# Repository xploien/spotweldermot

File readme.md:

# Spotwelder 
design progress of a MOT based spot welder 

## Feautres / Roadmap 

- [] precise digital control
- [] casing / enclosure 
- [] manual mode 
- [] cheap / easy to make as posible 

## Notes 

teoretical circuit is up, some simulation regarding the zero cross voltage detector have been done in circuit simulato Qucs-s
, power control baord needs X class capacitors to be safer, case is going to be hard since Mot transformer is really heavy. 

### some design concepts (Not final Product)

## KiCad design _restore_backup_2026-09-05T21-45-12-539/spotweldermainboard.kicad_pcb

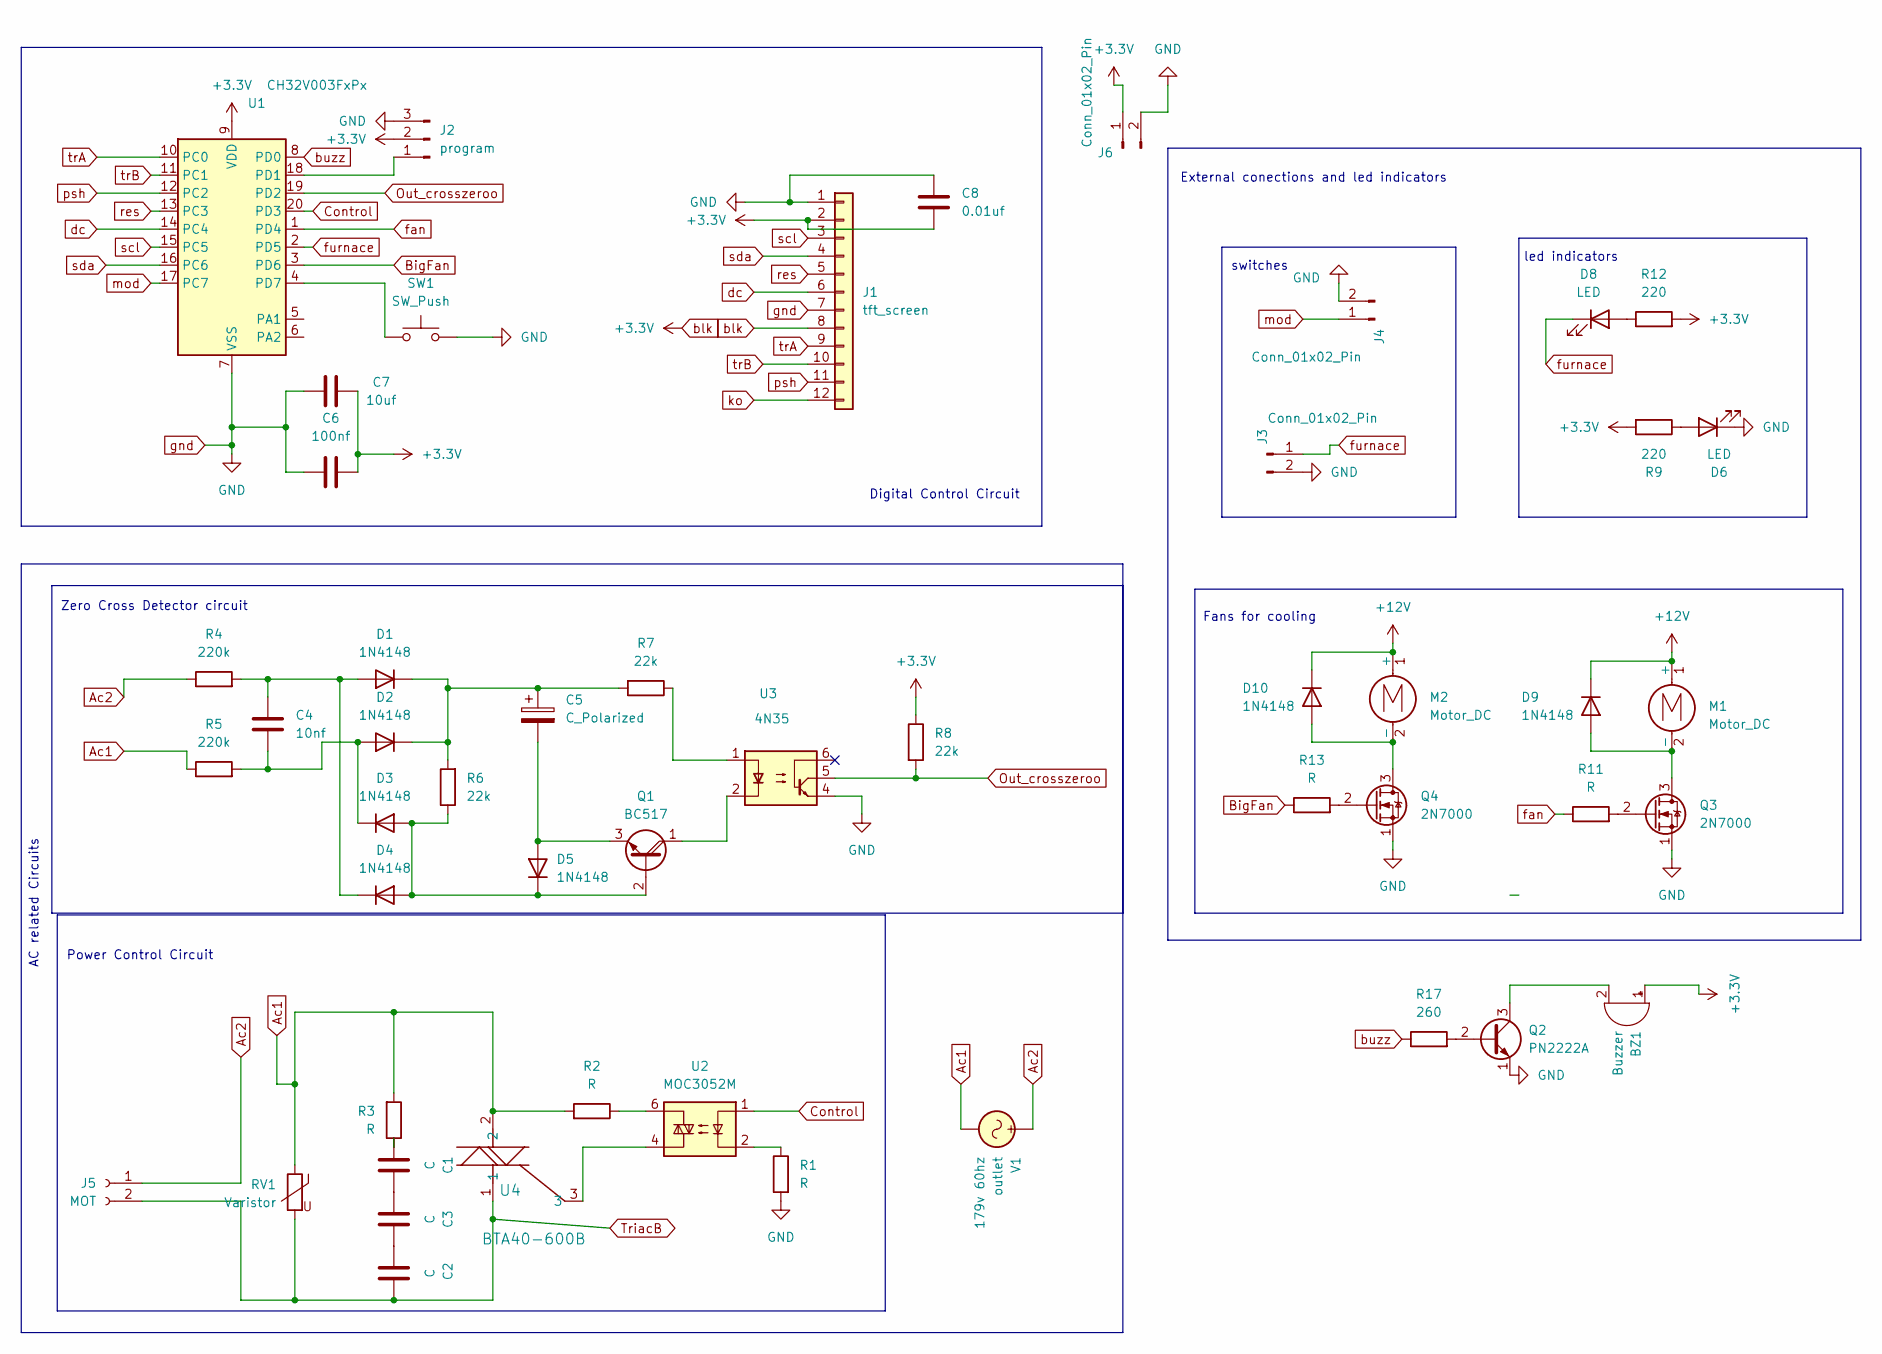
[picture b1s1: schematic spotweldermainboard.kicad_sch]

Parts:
BZ1: Buzzer; Buzzer_12x9.5RM7.6
C1, C2, C3: C; C_Rect_L18.0mm_W9.0mm_P15.00mm_FKS3_FKP3
C4: 10nf; C_Disc_D5.0mm_W2.5mm_P5.00mm
C5: C_Polarized; CP_Radial_D4.0mm_P2.00mm
C6: 100nf; CP_Radial_D4.0mm_P2.00mm
C7: 10uf; CP_Radial_D4.0mm_P2.00mm
C8: 0.01uf; C_Disc_D5.0mm_W2.5mm_P5.00mm
D1, D2, D3, D4, D5, D9, D10: 1N4148; D_DO-35_SOD27_P7.62mm_Horizontal
D6, D8: LED; LED_0402_1005Metric_Pad0.77x0.64mm_HandSolder
J1: tft_screen; PinSocket_1x12_P2.54mm_Horizontal
J2: program; PinHeader_1x03_P2.54mm_Vertical
J3, J4, J6: Conn_01x02_Pin; TerminalBlock_Phoenix_MKDS-1,5-2-5.08_1x02_P5.08mm_Horizont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
J5: MOT; TerminalBlock_Phoenix_MKDS-1,5-3_1x03_P5.00mm_Horizontal
M1, M2: Motor_DC; TerminalBlock_Phoenix_MKDS-1,5-2-5.08_1x02_P5.08mm_Horizont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
Q1: BC517; TO-92_Inline_Horizontal1
Q2: PN2222A; TO-92_Inline_Horizontal1
Q3, Q4: 2N7000; TO-92_Inline_Horizontal1
R1, R2, R3, R11, R13: R; R_Axial_DIN0207_L6.3mm_D2.5mm_P7.62mm_Horizontal
R4, R5: 220k; R_Axial_DIN0207_L6.3mm_D2.5mm_P7.62mm_Horizontal
R6, R7, R8: 22k; R_Axial_DIN0207_L6.3mm_D2.5mm_P7.62mm_Horizontal
R9, R12: 220; R_Axial_DIN0207_L6.3mm_D2.5mm_P7.62mm_Horizontal
R17: 260; R_Axial_DIN0207_L6.3mm_D2.5mm_P10.16mm_Horizontal
RV1: Varistor; R_Axial_DIN0207_L6.3mm_D2.5mm_P10.16mm_Horizontal
SW1: SW_Push; SW_SPST_CK_RS282G05A3
U1: CH32V003FxPx; TSSOP-20_4.4x6.5mm_P0.65mm
U2: MOC3052M; DIP-6_W7.62mm
U3: 4N35; DIP-6_W7.62mm
U4: BTA40-600B; RD91_STM
V1: outlet; TerminalBlock_Phoenix_MKDS-1,5-3_1x03_P5.00mm_Horizontal

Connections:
+12V: D9.1 (K), D10.1 (K), M1.1 (+), M2.1 (+)
Ac1: R2.2, R3.2, R5.1, RV1.1, U4.2, V1.2
Ac2: J5.1, R4.1, V1.1
BigFan: R13.1, U1.3 (PD6)
Control: U1.20 (PD3), U2.1
unnamed: BZ1.2 (-), Q2.3 (C)
unnamed: C1.1, C3.2
unnamed: C1.2, R3.1
unnamed: C2.2, C3.1
unnamed: C4.1, D1.2 (A), D4.1 (K), R4.2
unnamed: C5.1, D1.1 (K), D2.1 (K), R6.2, R7.2
unnamed: C4.2, D2.2 (A), D3.1 (K), R5.2
unnamed: D3.2 (A), D4.2 (A), D5.1 (K), Q1.2 (B), R6.1
unnamed: C5.2, D5.2 (A), Q1.3 (E)
unnamed: D6.2 (A), R9.1
unnamed: D8.2 (A), R12.1
unnamed: D9.2 (A), M1.2 (-), Q3.3 (D)
unnamed: D10.2 (A), M2.2 (-), Q4.3 (D)
unnamed: J2.1, U1.18 (PD1)
unnamed: Q1.1 (C), U3.2
unnamed: Q2.2 (B), R17.2
unnamed: Q3.2 (G), R11.2
unnamed: Q4.2 (G), R13.2
unnamed: R1.1, U2.2
unnamed: R2.1, U2.6
unnamed: R7.1, U3.1
unnamed: SW1.1, U1.4 (PD7)
unnamed: U2.4, U4.3
Out_crosszeroo: R8.2, U1.19 (PD2), U3.5
TriacB: C2.1, J5.2, RV1.2, U4.1
blk: BZ1.1 (+), C6.1, C7.1, C8.2, J1.2 (Vcc), J1.8 (BLK), J2.2, J6.1, R8.1, R9.2, R12.2, U1.9 (VDD)
buzz: R17.1, U1.8 (PD0)
dc: J1.6 (DC), U1.14 (PC4)
fan: R11.1, U1.1 (PD4)
furnace: D8.1 (K), J3.1, U1.2 (PD5)
gnd: C6.2, C7.2, C8.1, D6.1 (K), J1.1 (GND), J1.7 (CS), J2.3, J3.2, J4.2, J6.2, Q2.1 (E), Q3.1 (S), Q4.1 (S), R1.2, SW1.2, U1.7 (VSS), U3.4
ko: J1.12 (K0)
mod: J4.1, U1.17 (PC7)
psh: J1.11 (PSH), U1.12 (PC2)
res: J1.5 (RES), U1.13 (PC3)
scl: J1.3 (SCL), U1.15 (PC5)
sda: J1.4 (SDA), U1.16 (PC6)
trA: J1.9 (TRA), U1.10 (PC0)
trB: J1.10 (TRB), U1.11 (PC1)

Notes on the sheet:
External conections and led indicators
Digital Control Circuit
Power Control Circuit
Zero Cross Detector circuit
Fans for cooling
led indicators
AC related Circuits
switches

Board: 2 copper layers, 50 parts (50 on the bottom side), 43 nets, no tracks yet.

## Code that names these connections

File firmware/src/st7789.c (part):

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#include "font5x7.h"
// CH32V003 Pin Definitions
#ifndef ST7789_NO_CS
#define PIN_CS 2 // PC2
#endif
#define PIN_RESET 3 // PC3
#define PIN_DC 4    // PC4
#define SPI_SCLK 5  // PC5
#define SPI_MOSI 6  // PC6

#define DATA_MODE() (GPIOC->BSHR |= 1 << PIN_DC)   // DC High
#define COMMAND_MODE() (GPIOC->BCR |= 1 << PIN_DC) // DC Low
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#define ST7789_RASET 0x2B     // Row Address Set
#define ST7789_RAMWR 0x2C     // Memory Write
#define ST7789_PLTAR 0x30     // Partial Area
#define ST7789_MADCTL 0x36    // Memory Data Access Control
#define ST7789_COLMOD 0x3A    // Interface Pixel Format
#define ST7789_RAMCTRL 0xB0   // RAM Control
#define ST7789_PORCTRL 0xB2   // Porch Setting
#define ST7789_GCTRL 0xB7     // Gate Control
#define ST7789_VCOMS 0xBB     // VCOMS Setting
#define ST7789_LCMCTRL 0xC0   // LCM Control
#define ST7789_VDVVRHEN 0xC2  // VDV and VRH Command Enable
#define ST7789_VRHS 0xC3      // VRH Set
#define ST7789_VDVS 0xC4      // VDV Set
#define ST7789_FRCTRL2 0xC6   // Frame Rate Control in Normal Mode
#define ST7789_PWCTRL1 0xD0   // Power Control 1
#define ST7789_PVGAMCTRL 0xE0 // Positive Voltage Gamma Control
#define ST7789_NVGAMCTRL 0xE1 // Negative Voltage Gamma Control

// MADCTL Parameters
#define ST7789_MADCTL_MH 0x04  // Bit 2 - Refresh Left to Right
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  RCC->APB2PCENR |= RCC_APB2Periph_GPIOC | RCC_APB2Periph_SPI1;

#ifndef ST7789_NO_CS
  // PC2 - CS
  GPIOC->CFGLR &= ~(0xf << (PIN_CS << 2));
  GPIOC->CFGLR |= (GPIO_CNF_OUT_PP | GPIO_Speed_50MHz) << (PIN_CS << 2);
#endif

  // PC3 - RESET
  GPIOC->CFGLR &= ~(0xf << (PIN_RESET << 2));
  GPIOC->CFGLR |= (GPIO_CNF_OUT_PP | GPIO_Speed_50MHz) << (PIN_RESET << 2);

  // PC4 - DC
  GPIOC->CFGLR &= ~(0xf << (PIN_DC << 2));
  GPIOC->CFGLR |= (GPIO_CNF_OUT_PP | GPIO_Speed_50MHz) << (PIN_DC << 2);

  // PC5 - SCLK
  GPIOC->CFGLR &= ~(0xf << (SPI_SCLK << 2));
  GPIOC->CFGLR |= (GPIO_CNF_OUT_PP_AF | GPIO_Speed_50MHz) << (SPI_SCLK << 2);

  // PC6 - MOSI
  GPIOC->CFGLR &= ~(0xf << (SPI_MOSI << 2));
  GPIOC->CFGLR |= (GPIO_CNF_OUT_PP_AF | GPIO_Speed_50MHz) << (SPI_MOSI << 2);

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
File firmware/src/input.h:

#pragma once

extern "C" {
#include "../ch32fun/ch32fun/ch32fun.h"
#include "st7789.h"
}

class inputdevices {
public:
// PC0 — Encoder A
#define ENC_A_PORT GPIOC
#define ENC_A_PIN 0

// PC1 — Encoder B  (antes PD1 = SWIO/debug — NO tocar)
#define ENC_B_PORT GPIOC
#define ENC_B_PIN 1

// PD2 — Encoder push
#define ENC_PUSH_PORT GPIOD
#define ENC_PUSH_PIN 2

// PD3 — Botón OK
#define BTN_OK_PORT GPIOD
#define BTN_OK_PIN 3

#define READ_PIN(port, pin) (((port)->INDR >> (pin)) & 1u)

  typedef enum {
    MENU_TIME = 0,
    MENU_MAGNITUDE = 1,
    MENU_PERCENTAGE = 2,
    MAX_STATES
  } selectmenus;

  static selectmenus current_menu;

  static inline void gpio_init(void) {
    RCC->APB2PCENR |= RCC_APB2Periph_GPIOC | RCC_APB2Periph_GPIOD;

    // PC0 — Enc A — input pull-up
    GPIOC->CFGLR =
        (GPIOC->CFGLR & ~(0xFu << (ENC_A_PIN * 4))) | (0x8u << (ENC_A_PIN * 4));
    GPIOC->BSHR = (1u << ENC_A_PIN);

    // PC1 — Enc B — input pull-up
    GPIOC->CFGLR =
        (GPIOC->CFGLR & ~(0xFu << (ENC_B_PIN * 4))) | (0x8u << (ENC_B_PIN * 4));
    GPIOC->BSHR = (1u << ENC_B_PIN);

    // PD2 — Enc Push — input pull-up
    GPIOD->CFGLR = (GPIOD->CFGLR & ~(0xFu << (ENC_PUSH_PIN * 4))) |
                   (0x8u << (ENC_PUSH_PIN * 4));
    GPIOD->BSHR = (1u << ENC_PUSH_PIN);

    // PD3 — Btn OK — input flotante (debounce HW externo)
    GPIOD->CFGLR = (GPIOD->CFGLR & ~(0xFu << (BTN_OK_PIN * 4))) |
                   (0x4u << (BTN_OK_PIN * 4));
  }

  static inline void isencoderpushed(void) {
    static uint32_t last_ms = 0;
    if (!(READ_PIN(ENC_PUSH_PORT, ENC_PUSH_PIN))) {
      uint32_t now = SysTick->CNT / (FUNCONF_SYSTEM_CORE_CLOCK / 1000);
      if ((now - last_ms) > 200) {
        last_ms = now;
        current_menu = (selectmenus)((current_menu + 1) % MAX_STATES);
      }
    }
  }

  static inline int encoder(void) {
    static uint8_t prev_A = 1;
    static int contador = 0;

    uint8_t A = READ_PIN(ENC_A_PORT, ENC_A_PIN);
    uint8_t B = READ_PIN(ENC_B_PORT, ENC_B_PIN);

    if (prev_A == 1 && A == 0) {
      if (B == 1) {
        contador++;
        tft_draw_thick_circle(119, 119, 30, 15, GREENYELLOW);
      } else {
        contador--;
        tft_draw_thick_circle(119, 119, 30, 15, RED);
      }
      Delay_Ms(5);
    }

    prev_A = A;
    return contador;
  }
};

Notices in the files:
firmware/src/st7789.c:
\copyright Attribution-NonCommercial-ShareAlike 4.0 (CC BY-NC-SA 4.0)
